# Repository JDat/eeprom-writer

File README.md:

Arduino I2C EEPROM Programmer for SST39SF010A/SST39SF020A/SST39SF040A AT29C010A

This code should be compiled by the Arduino IDE and run on an Arduino UNO.

Code based on:
http://danceswithferrets.org/geekblog/?page_id=903
https://github.com/TSwimson/eeprom-writer

and Chris Baird’s Python script

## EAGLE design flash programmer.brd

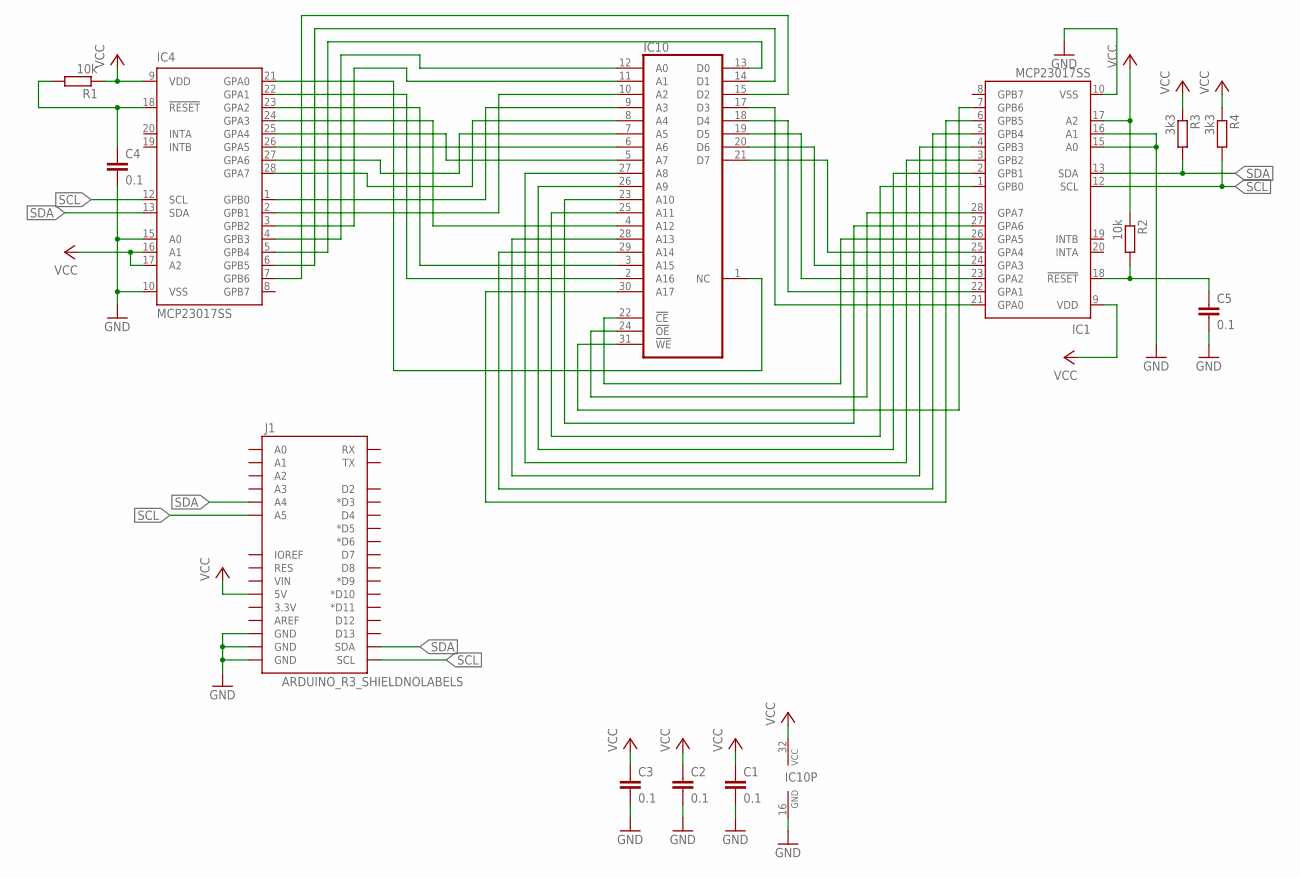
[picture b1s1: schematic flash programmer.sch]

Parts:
C1, C2, C3, C4, C5: 0.1; C0603
IC1, IC4: MCP23017SS; SSOP28
IC10: SST39SF020A-70-4C-PHE; DIL32
J1: ARDUINO_R3_SHIELDNOLABELS; UNO_R3_SHIELD_NOLABELS
R1, R2: 10k; R0603
R3, R4: 3k3; R0603

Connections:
GND: C1.2, C2.2, C3.2, C4.2, C5.2, IC1.10 (VSS), IC1.15 (A0), IC1.16 (A1), IC4.10 (VSS), IC4.15 (A0), IC10.16 (GND), J1.GND@0 (GND), J1.GND@1 (GND), J1.GND@2 (GND)
unnamed: IC4.21 (GPA0), IC10.1 (NC)
unnamed: IC4.22 (GPA1), IC10.2 (A16)
unnamed: IC4.23 (GPA2), IC10.3 (A15)
unnamed: IC4.24 (GPA3), IC10.4 (A12)
unnamed: IC4.25 (GPA4), IC10.5 (A7)
unnamed: IC4.26 (GPA5), IC10.6 (A6)
unnamed: IC4.27 (GPA6), IC10.7 (A5)
unnamed: IC4.28 (GPA7), IC10.8 (A4)
unnamed: IC4.2 (GPB1), IC10.10 (A2)
unnamed: IC4.1 (GPB0), IC10.9 (A3)
unnamed: IC4.3 (GPB2), IC10.11 (A1)
unnamed: IC4.4 (GPB3), IC10.12 (A0)
unnamed: IC4.5 (GPB4), IC10.13 (D0)
unnamed: IC4.6 (GPB5), IC10.14 (D1)
unnamed: IC4.7 (GPB6), IC10.15 (D2)
unnamed: IC1.21 (GPA0), IC10.17 (D3)
unnamed: IC1.22 (GPA1), IC10.18 (D4)
unnamed: IC1.23 (GPA2), IC10.19 (D5)
unnamed: IC1.24 (GPA3), IC10.20 (D6)
unnamed: IC1.25 (GPA4), IC10.21 (D7)
unnamed: IC1.26 (GPA5), IC10.22 (!CE)
unnamed: IC1.27 (GPA6), IC10.23 (A10)
unnamed: IC1.28 (GPA7), IC10.24 (!OE)
unnamed: IC1.1 (GPB0), IC10.25 (A11)
unnamed: IC1.2 (GPB1), IC10.26 (A9)
unnamed: IC1.3 (GPB2), IC10.27 (A8)
unnamed: IC1.4 (GPB3), IC10.28 (A13)
unnamed: IC1.5 (GPB4), IC10.29 (A14)
unnamed: IC1.6 (GPB5), IC10.30 (A17)
unnamed: IC1.7 (GPB6), IC10.31 (!WE)
unnamed: C5.1, IC1.18 (!RESET), R2.2
unnamed: C4.1, IC4.18 (!RESET), R1.2
SCL: IC1.12 (SCL), IC4.12 (SCL), J1.A5, J1.SCL, R4.2
SDA: IC1.13 (SDA), IC4.13 (SDA), J1.A4, J1.SDA, R3.2
VCC: C1.1, C2.1, C3.1, IC1.9 (VDD), IC1.17 (A2), IC4.9 (VDD), IC4.16 (A1), IC4.17 (A2), IC10.32 (VCC), J1.5V, R1.1, R2.1, R3.1, R4.1

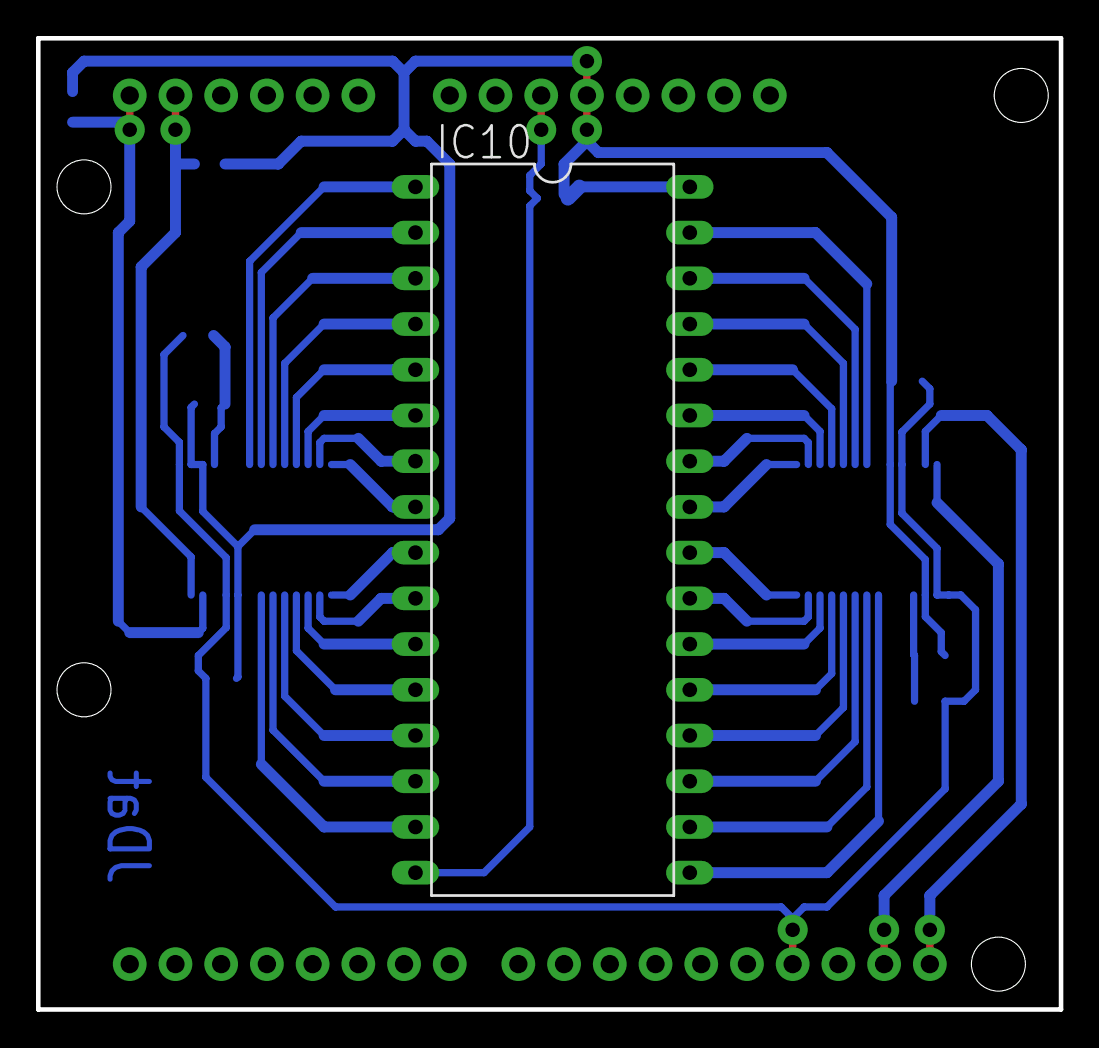
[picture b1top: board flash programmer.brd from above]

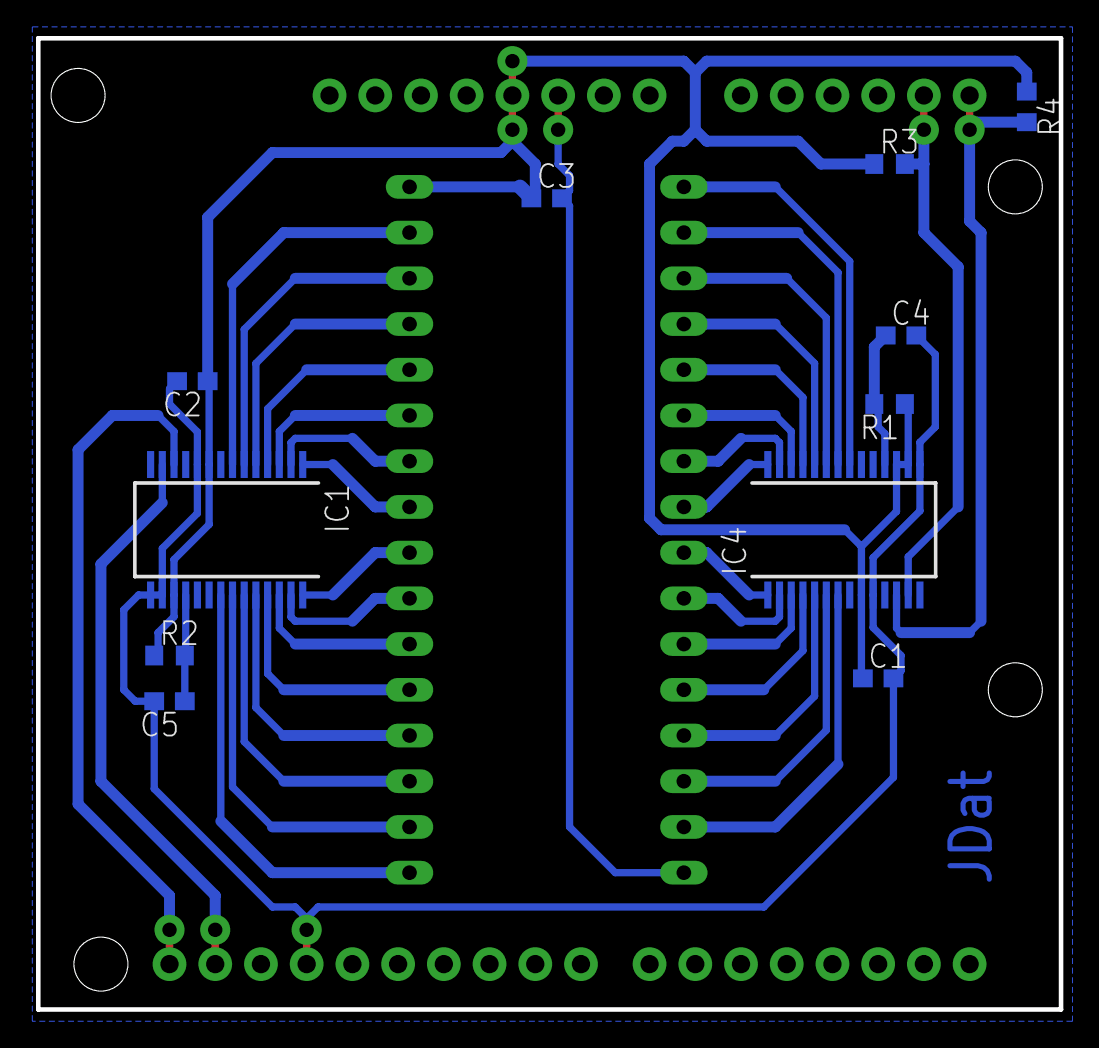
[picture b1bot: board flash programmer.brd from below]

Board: 2 copper layers, 56.8 x 54.0 mm, 13 parts (11 on the bottom side), 36 nets.

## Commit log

2019-04-08 1st working version.
    Firmware is working.
    Need to optimize for speed.
    Still some bugs in Python code and optimisations with serial port.

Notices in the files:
parts and their libraries:
SparkFun-Boards: Licensing: Creative Commons ShareAlike 4.0 International - https://creativecommons.org/licenses/by-sa/4.0
